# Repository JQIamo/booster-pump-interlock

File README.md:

# Booster Pump Interlock

Booster pump interlock design files. The board is a simple RS latch interlock that reads an open/closed status from a NESLAB Thermoflex 5000 and controls power to a [Berkeley High Pressure Booster Pump](http://www.berkeleypumps.com/ResidentialProduct_Series_MGP_MGPS.aspx).

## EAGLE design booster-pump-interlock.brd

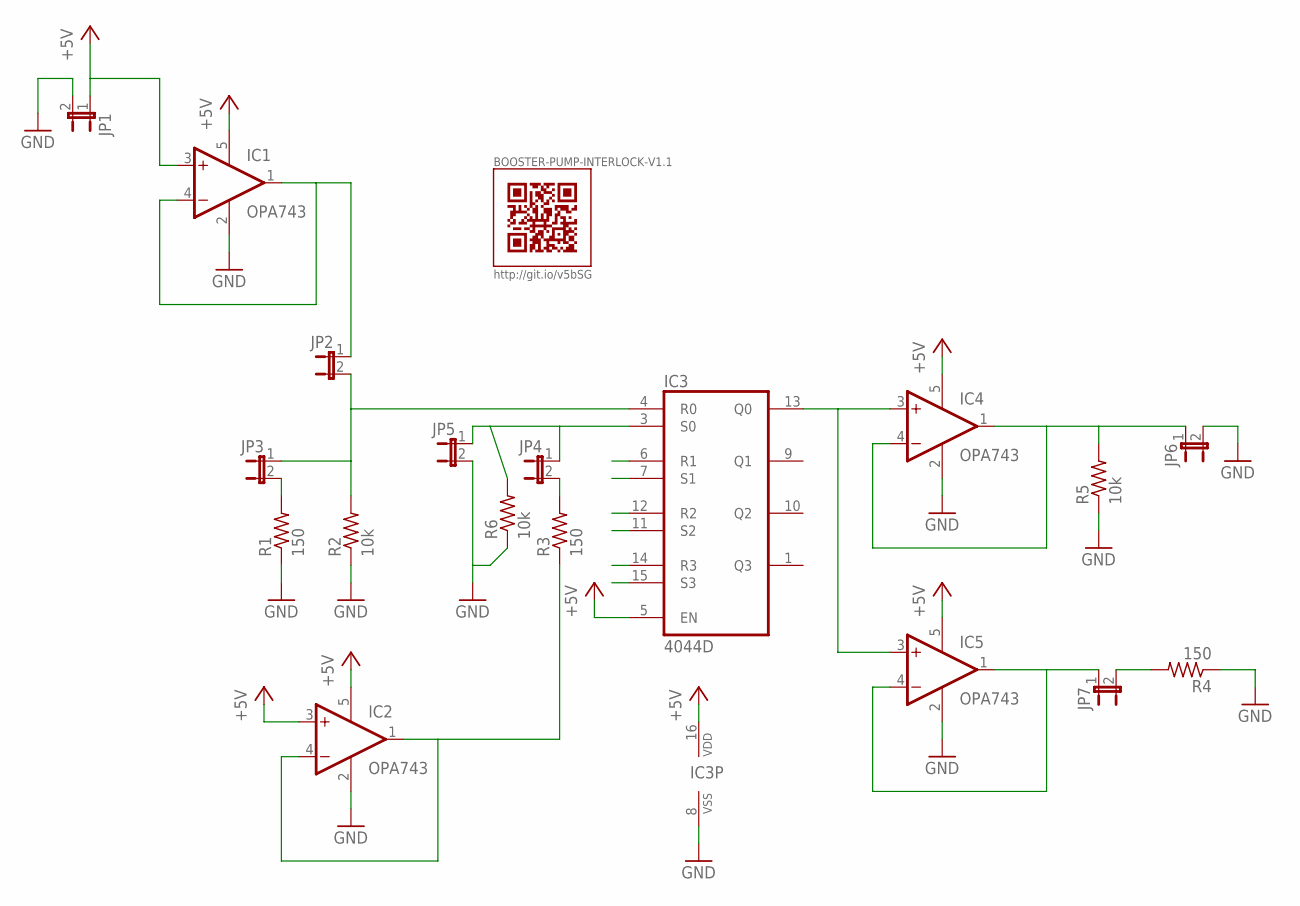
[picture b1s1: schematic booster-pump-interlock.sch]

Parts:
BOOSTER-PUMP-INTERLOCK-V1.1: QR-HTTP://GIT.IO/V5BSG-WIRE
IC1, IC2, IC4, IC5: OPA743; SOT23-5
IC3: 4044D; SO16
JP1, JP2, JP3, JP4, JP5, JP6, JP7: JP1E; JP1
R1, R3, R4: 150; R0805
R2, R5: 10k; R0805
R6: 10k; M1206

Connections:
+5V: IC1.3 (+IN), IC1.5 (V+), IC2.3 (+IN), IC2.5 (V+), IC3.5 (EN), IC3.16 (VDD), IC4.5 (V+), IC5.5 (V+), JP1.1
GND: IC1.2 (V-), IC2.2 (V-), IC3.6 (R1), IC3.7 (S1), IC3.8 (VSS), IC3.11 (S2), IC3.12 (R2), IC3.14 (R3), IC3.15 (S3), IC4.2 (V-), IC5.2 (V-), JP1.2, JP5.2, JP6.2, R1.1, R2.1, R4.1, R5.1, R6.1
unnamed: JP3.2, R1.2
unnamed: JP4.2, R3.2
unnamed: IC4.1 (OUT), IC4.4 (-IN), JP6.1, R5.2
unnamed: JP7.2, R4.2
unnamed: IC5.1 (OUT), IC5.4 (-IN), JP7.1
PWR1: IC1.1 (OUT), IC1.4 (-IN), JP2.1
PWR2: IC2.1 (OUT), IC2.4 (-IN), R3.1
Q0: IC3.13 (Q0), IC4.3 (+IN), IC5.3 (+IN)
R0: IC3.4 (R0), JP2.2, JP3.1, R2.2
S0: IC3.3 (S0), JP4.1, JP5.1, R6.2

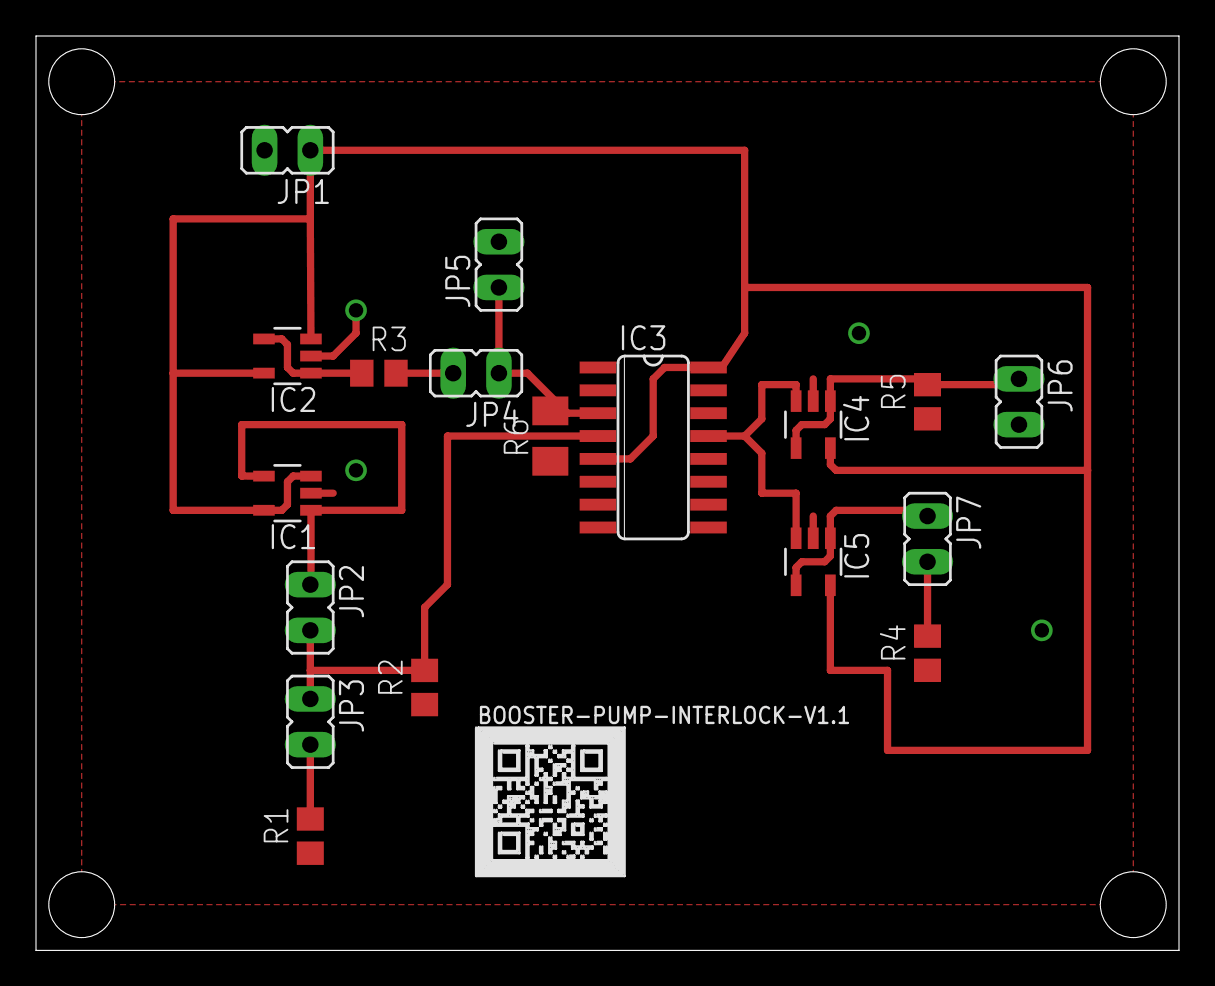
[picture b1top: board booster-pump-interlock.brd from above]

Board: 2 copper layers, 63.5 x 50.8 mm, 19 parts (0 on the bottom side), 12 nets.

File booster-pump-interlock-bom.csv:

"Part";"Value";"Device";"Package";"Description";"PARTNO";"QR_DEST";"QR_DEST_SHORT";
"BOOSTER-PUMP-INTERLOCK-V1.1";"QR-HTTP://GIT.IO/V5BSG-WIRE";"QR-HTTP://GIT.IO/V5BSG-WIRE";"QR-HTTP://GIT.IO/V5BSG-WIRE";"QR Code pointing to http://git.io/v5bSG-WIRE if a wire-based rendering for silks screens lighter than the solder mask.";"";"http://git.io/v5bSG";"git.io/v5bSG";
"IC1";"OPA743";"OPA743";"SOT23-5";"12V, 7MHz, CMOS, Rail-to-Rail I/O OP AMP";"OPA743NA/3KCT-ND";"";"";
"IC2";"OPA743";"OPA743";"SOT23-5";"12V, 7MHz, CMOS, Rail-to-Rail I/O OP AMP";"OPA743NA/3KCT-ND";"";"";
"IC3";"4044D";"4044D";"SO16";"Quad 3-state NAND R/S LATCH";"";"";"";
"IC4";"OPA743";"OPA743";"SOT23-5";"12V, 7MHz, CMOS, Rail-to-Rail I/O OP AMP";"OPA743NA/3KCT-ND";"";"";
"IC5";"OPA743";"OPA743";"SOT23-5";"12V, 7MHz, CMOS, Rail-to-Rail I/O OP AMP";"OPA743NA/3KCT-ND";"";"";
"JP1";"";"JP1E";"JP1";"JUMPER";"";"";"";
"JP2";"";"JP1E";"JP1";"JUMPER";"";"";"";
"JP3";"";"JP1E";"JP1";"JUMPER";"";"";"";
"JP4";"";"JP1E";"JP1";"JUMPER";"";"";"";
"JP5";"";"JP1E";"JP1";"JUMPER";"";"";"";
"JP6";"";"JP1E";"JP1";"JUMPER";"";"";"";
"JP7";"";"JP1E";"JP1";"JUMPER";"";"";"";
"R1";"150";"R-US_R0805";"R0805";"RESISTOR, American symbol";"";"";"";
"R2";"10k";"R-US_R0805";"R0805";"RESISTOR, American symbol";"";"";"";
"R3";"150";"R-US_R0805";"R0805";"RESISTOR, American symbol";"";"";"";
"R4";"150";"R-US_R0805";"R0805";"RESISTOR, American symbol";"";"";"";
"R5";"10k";"R-US_R0805";"R0805";"RESISTOR, American symbol";"";"";"";

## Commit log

2017-09-18 first commit!
2017-09-18 added README
2017-09-19 added front panel.
2017-09-19 added QR code & tag.
2019-05-14 Added pulldown resistor to fix tripping issue due to charge buildup on pulldown diode
